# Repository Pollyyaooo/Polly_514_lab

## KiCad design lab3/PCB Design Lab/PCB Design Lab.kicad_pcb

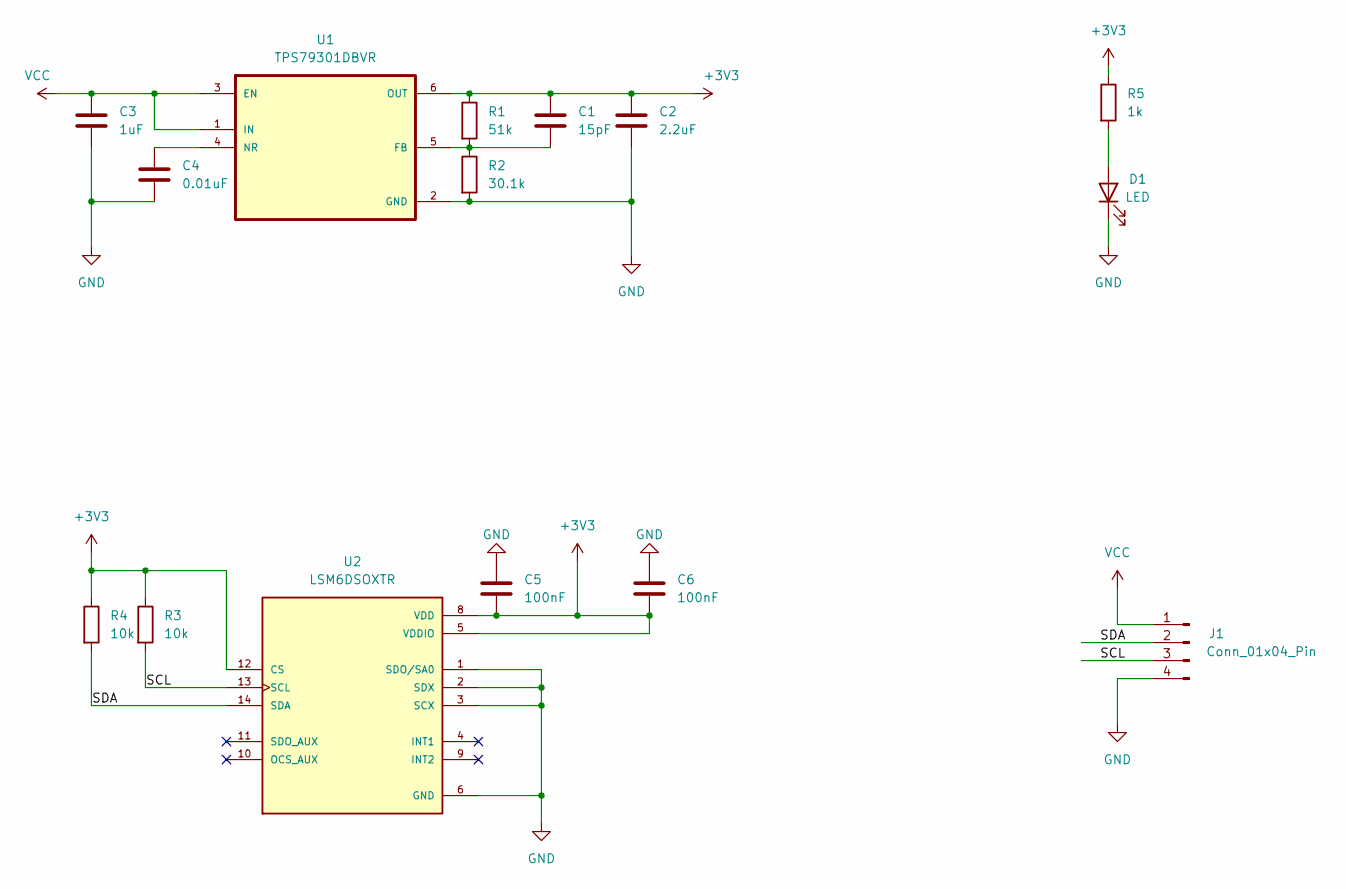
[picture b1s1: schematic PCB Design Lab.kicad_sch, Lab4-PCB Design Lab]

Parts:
C1: 15pF; C_0402_1005Metric_Pad0.74x0.62mm_HandSolder
C2: 2.2uF; C_0402_1005Metric_Pad0.74x0.62mm_HandSolder
C3: 1uF; C_0402_1005Metric_Pad0.74x0.62mm_HandSolder
C4: 0.01uF; C_0402_1005Metric_Pad0.74x0.62mm_HandSolder
C5, C6: 100nF; C_0402_1005Metric_Pad0.74x0.62mm_HandSolder
D1: LED; LED_0402_1005Metric_Pad0.77x0.64mm_HandSolder
J1: Conn_01x04_Pin; PinSocket_1x04_P2.54mm_Vertical
R1: 51k; R_0402_1005Metric_Pad0.72x0.64mm_HandSolder
R2: 30.1k; R_0402_1005Metric_Pad0.72x0.64mm_HandSolder
R3, R4: 10k; R_0402_1005Metric_Pad0.72x0.64mm_HandSolder
R5: 1k; R_0402_1005Metric_Pad0.72x0.64mm_HandSolder
U1: TPS79301DBVR; SOT95P280X145-6N; DigiKey_Part_Number 296-12154-1-ND
U2: LSM6DSOXTR; PQFN50P250X300X86-14N; PARTREV 3.0; DigiKey_Part_Number 497-18367-1-ND

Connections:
+3V3: C1.1, C2.1, C5.2, C6.2, R1.1, R3.1, R4.1, R5.1, U1.6 (OUT), U2.5 (VDDIO), U2.8 (VDD), U2.12 (CS)
/SCL: J1.3, R3.2, U2.13 (SCL)
/SDA: J1.2, R4.2, U2.14 (SDA)
GND: C2.2, C3.2, C4.2, C5.1, C6.1, D1.1 (K), J1.4, R2.2, U1.2 (GND), U2.1 (SDO/SA0), U2.2 (SDX), U2.3 (SCX), U2.6 (GND), U2.7 (GND)
unnamed: D1.2 (A), R5.2
unnamed: C1.2, R1.2, R2.1, U1.5 (FB)
unnamed: C4.1, U1.4 (NR)
VCC: C3.1, J1.1, U1.1 (IN), U1.3 (EN)

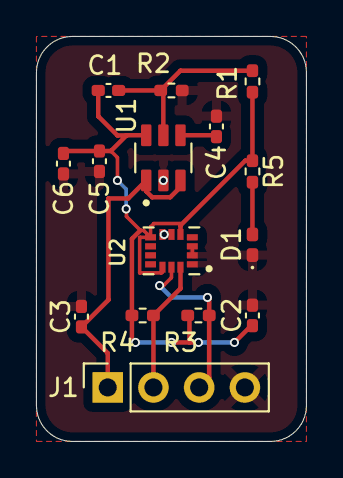
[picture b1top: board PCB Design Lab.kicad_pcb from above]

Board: 2 copper layers, 15.0 x 22.5 mm, 15 parts (0 on the bottom side), 8 nets.

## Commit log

2026-01-13 Add Lab 2: component selection, soldering, and ESP32 ADC reading
2026-01-29 PCB update
2026-01-29 gerbers
2026-02-02 lab3 update
2026-02-04 lab5 add
2026-02-04 API remove
